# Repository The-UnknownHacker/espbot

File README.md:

# Battlebot

**Author:** Aarav J
**GitHub:** [espbot](https://github.com/The-UnknownHacker/espbot)  
**Started:** July 20, 2025  
**Finished:** August 8, 2025  
**Time Invested:** 7h 10m  

---

## Overview

This project is a custom **battlebot PCB** built around the **ESP32-C3** module.  
The board communicates with a remote and drives motors using an **L293D motor driver**, with an additional relay port for expansion.  
A custom case was designed in Fusion 360 to house the PCB securely.  

---

## Features

- **Microcontroller:** ESP32-C3 (Xiao module)  
- **Motor Driver:** L293D  
- **Expansion:** Relay port for add-ons  
- **PCB:** Single-sided routing on B.Cu layer for a clean look  
- **Case:** Fusion 360 CAD case with fillets and size adjustments  

---

## Repository Contents

- **Schematics & PCB** — KiCad project files  
- **Fabrication Settings** — ready for PCB manufacturing  
- **CAD Models** — Fusion 360 case design  

---

## Time Breakdown

- **Schematic Design:** 1h 40m  
- **PCB Layout:** 2h 20m  
- **Fusion Case:** 2h 0m  
- **Case Finalization:** 1h 10m  
- **Total:** 7h 10m  

---

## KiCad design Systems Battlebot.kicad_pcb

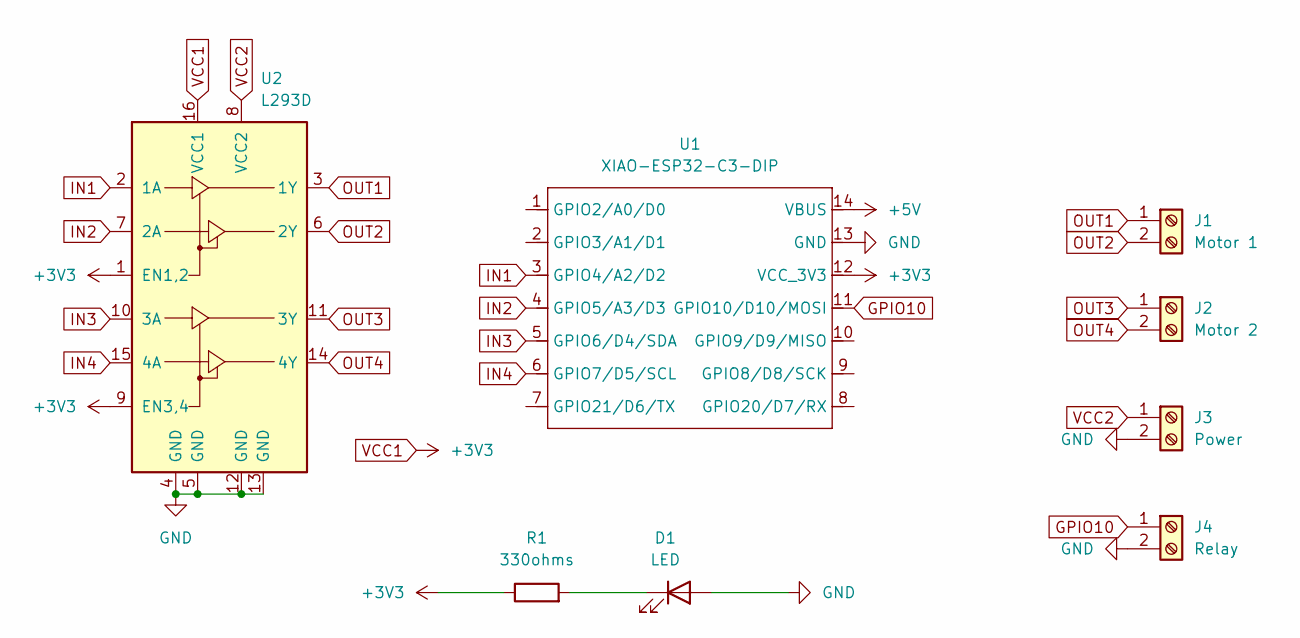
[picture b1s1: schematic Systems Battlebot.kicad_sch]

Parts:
D1: LED; LED_D3.0mm
J1: Motor 1; TerminalBlock_Altech_AK300-2_P5.00mm
J2: Motor 2; TerminalBlock_Altech_AK300-2_P5.00mm
J3: Power; TerminalBlock_Altech_AK300-2_P5.00mm
J4: Relay; TerminalBlock_Altech_AK300-2_P5.00mm
R1: 330ohms; R_Axial_DIN0207_L6.3mm_D2.5mm_P7.62mm_Horizontal
U1: XIAO-ESP32-C3-DIP; XIAO-ESP32C3-DIP
U2: L293D; DIP-16_W7.62mm

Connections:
+5V: U1.14 (VBUS)
GND: D1.2 (A), J3.2, J4.2, U1.13 (GND), U2.4 (GND), U2.5 (GND), U2.12 (GND), U2.13 (GND)
GPIO10: J4.1, U1.11 (GPIO10/D10/MOSI)
IN1: U1.3 (GPIO4/A2/D2), U2.2 (1A)
IN2: U1.4 (GPIO5/A3/D3), U2.7 (2A)
IN3: U1.5 (GPIO6/D4/SDA), U2.10 (3A)
IN4: U1.6 (GPIO7/D5/SCL), U2.15 (4A)
unnamed: D1.1 (K), R1.2
OUT1: J1.1, U2.3 (1Y)
OUT2: J1.2, U2.6 (2Y)
OUT3: J2.1, U2.11 (3Y)
OUT4: J2.2, U2.14 (4Y)
VCC1: R1.1, U1.12 (VCC_3V3), U2.1 (EN1,2), U2.9 (EN3,4), U2.16 (VCC1)
VCC2: J3.1, U2.8 (VCC2)

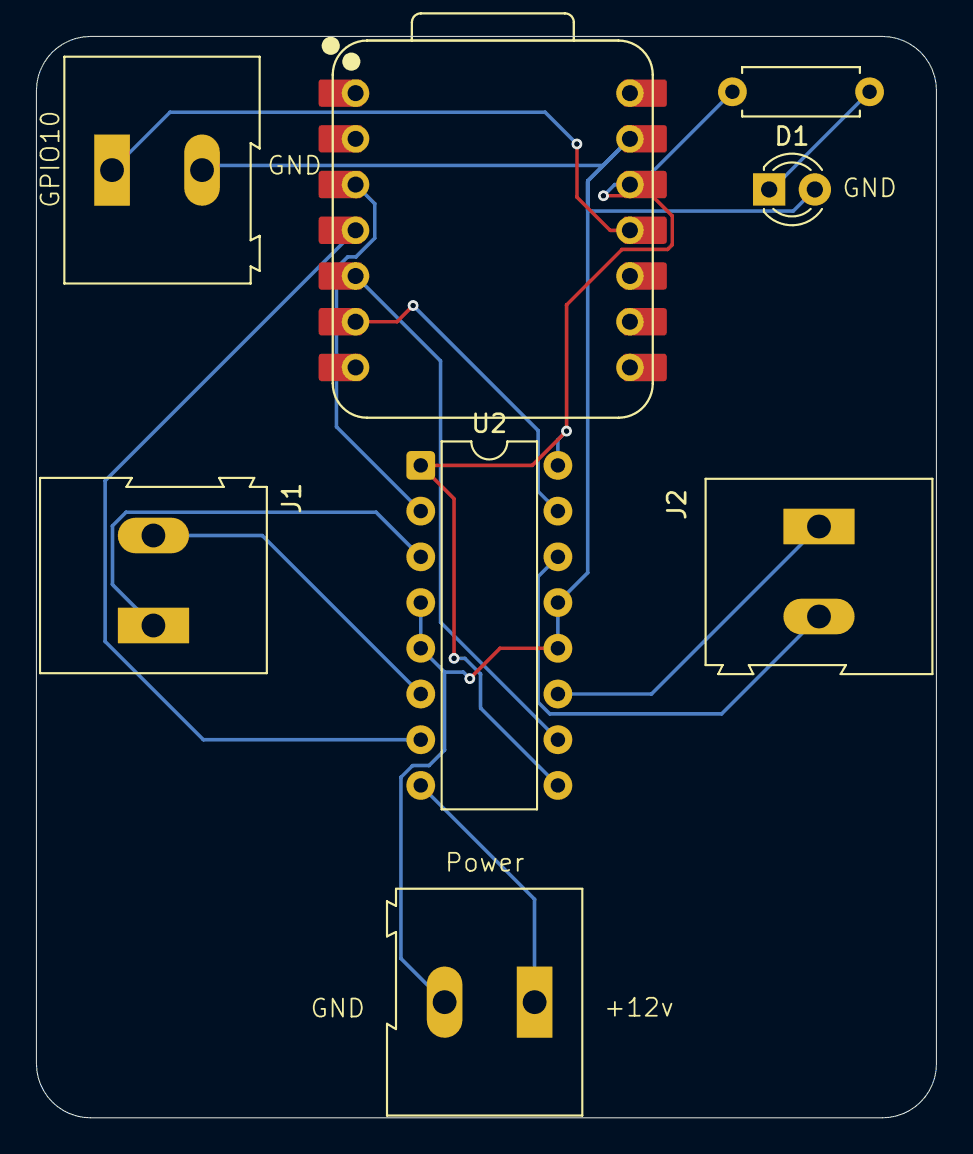
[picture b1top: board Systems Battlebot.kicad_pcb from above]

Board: 2 copper layers, 50.0 x 60.1 mm, 8 parts (0 on the bottom side), 13 nets.

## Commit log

2025-07-21 Add files
